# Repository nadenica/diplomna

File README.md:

Машина за рециклиране на пластмасови бутилки

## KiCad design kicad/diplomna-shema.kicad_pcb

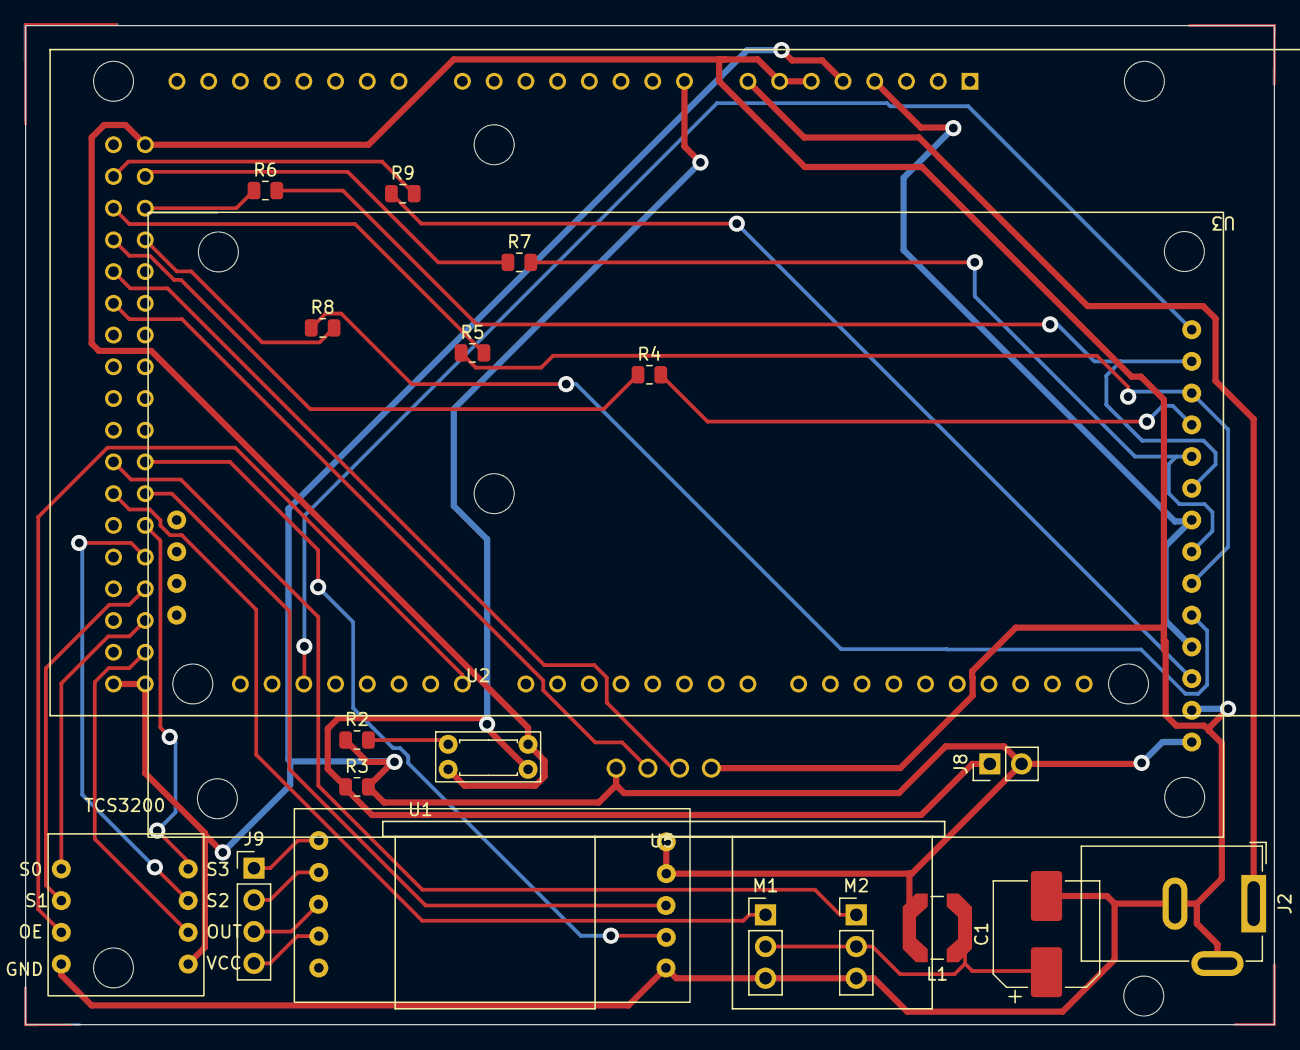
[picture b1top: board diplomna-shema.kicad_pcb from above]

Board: 2 copper layers, 100.0 x 80.0 mm, 21 parts (0 on the bottom side), 36 nets.

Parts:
A1: Arduino Mega; arduino_mega2560
C1: C; CP_Elec_8x5.4
J2: Power input 5VDC; BarrelJack_GCT_DCJ200-10-A_Horizontal
J8: PinHeader_1x02_P2.54mm_Vertical
J9: PinHeader_1x04_P2.54mm_Vertical
L1: L; L_Coilcraft_LPS5030
M1: Motor_rampa; PinHeader_1x03_P2.54mm_Vertical
M2: Futuba S3003; PinHeader_1x03_P2.54mm_Vertical
R2: 100Ω; R_0805_2012Metric
R3, R5, R6, R7, R8, R9: 10kΩ; R_0805_2012Metric
R4: 10k; R_0805_2012Metric
U1: HC-SR04; XCVR_HC-SR04
U2: TCRT5000; TCS3200
U3: LCD-TFT-2.8inch; 2.8inch_tft-lcd
U4: TCS3200; TCS3200 color sensor
U5: HX711

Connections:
+3.3V: A1.3V3 (+3V3), U3.4 (PIN), U3.8 (PIN)
+5V: A1.5V_1 (+5V_1), A1.5V_2 (+5V_2), A1.5V_3 (+5V_3), J8.2, L1.2, R2.1, R3.2, U1.1 (VCC), U3.1 (PIN), U4.5 (VDD), U5.6 (PIN), U5.7 (PIN)
GND: A1.GND1, A1.GND2, A1.GND3, A1.GND4, C1.2, J2.2, J2.3, M1.3 (-), M2.3 (-), U1.4 (GND), U2.2, U2.3, U3.2 (PIN), U4.4 (GND), U5.10 (PIN)
unnamed: A1.48, R8.2
unnamed: A1.49, R4.1
unnamed: A1.50, R6.1
unnamed: A1.51, R5.2
unnamed: A1.52, R7.1
unnamed: A1.53, R9.2
unnamed: A1.AD0, J8.1, R3.1, U2.4
unnamed: A1.VIN, J2.1
unnamed: J9.1, U5.1 (PIN)
unnamed: J9.4, U5.4 (PIN)
unnamed: J9.2, U5.2 (PIN)
unnamed: J9.3, U5.3 (PIN)
unnamed: C1.1, L1.1, M1.2 (+), M2.2 (+)
unnamed: A1.33, M1.1 (PWM)
unnamed: A1.35, M2.1 (PWM)
unnamed: R2.2, U2.1
unnamed: A1.47, U1.3 (ECHO)
unnamed: A1.45, U1.2 (TRIG)
unnamed: R9.1, U3.3 (PIN)
unnamed: R8.1, U3.5 (PIN)
unnamed: R7.2, U3.7 (PIN), U3.10 (PIN)
unnamed: R4.2, U3.11 (PIN)
unnamed: R5.1, U3.6 (PIN), U3.12 (PIN)
unnamed: R6.2, U3.9 (PIN), U3.13 (PIN)
unnamed: A1.19, U3.14 (PIN)
unnamed: A1.22, U4.6 (OUT)
unnamed: A1.24, U4.1 (S0)
unnamed: A1.26, U4.2 (S1)
unnamed: A1.28, U4.7 (S2)
unnamed: A1.30, U4.8 (S3)
unnamed: A1.14, U4.3 (~OE)
unnamed: A1.32, U5.8 (PIN)
unnamed: A1.34, U5.9 (PIN)

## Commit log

2024-05-20 последна версия - корекции по платка и схема, нови 3Dчасти за конструкция със сменен мотор и преправен код
